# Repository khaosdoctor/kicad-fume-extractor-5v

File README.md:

# Fume Extractor 5V

KiCad project for a small, battery-powered fume extractor: a 9V battery feeds an
L7805 linear regulator to drive a 5V fan through a BC337 transistor, with a
potentiometer for speed control, a trimmer for calibration, a power switch and
an LED indicator.

This is my first electronics project, so it's a work in progress. Expect
multiple revisions as the design gets refined.

## PCB preview

| Top | Bottom |
|-----|--------|
|  |  |

## Hardware overview

Interactive BOM: [khaosdoctor.github.io/kicad-fume-extractor-5v/bom/ibom.html](https://khaosdoctor.github.io/kicad-fume-extractor-5v/bom/ibom.html)

| Ref  | Part                     | Function                        |
|------|--------------------------|----------------------------------|
| BT1  | 9V battery cell          | Power source                     |
| U1   | L7805ACV                 | 5V linear regulator               |
| Q1   | BC337                    | Fan drive transistor              |
| J1   | 2-pin connector          | Fan output                        |
| RV1  | 500R potentiometer       | Fan speed control                 |
| RV2  | 1K trimmer               | Calibration                       |
| R1   | 350R resistor            | Bias/current limiting             |
| C1/C2| Capacitors               | Regulator input/output filtering  |
| D1   | LED                      | Power indicator                   |
| SW1  | SPST switch              | Power on/off                      |

The board is a 2-layer PCB designed in KiCad 10.

## Generating manufacturing files with KiBot

This project uses [KiBot](https://github.com/INTI-CMNB/KiBot) to generate
gerbers, drill files, pick & place, BOM, documentation and 3D outputs
straight from the KiCad source files, via `kibot.yaml`.

### Outputs produced

| Group           | Outputs                                                        | Directory              |
|-----------------|------------------------------------------------------------------|-------------------------|
| `fabrication`   | Gerbers, Excellon drill files                                    | `Manufacturing/Gerbers` |
| `assembly`      | Pick & place position file, BOM (CSV)                            | `Manufacturing/Assembly`|
| `documentation` | Schematic PDF, PCB PDF, interactive HTML BOM                      | `Documentation`, `bom`  |
| `3d`            | STEP model, top/bottom 3D renders                                 | `3D`                    |

A zipped bundle of gerbers + drill files ready to send to a fab house is also
produced under `Manufacturing/manufacturing_zip.zip`. A JLCPCB-specific BOM
(`bom_jlcpcb`) filtered to parts with an LCSC part number is available but not
run by default.

### Running locally

Install KiCad (10.x) and KiBot, then from the repository root run:

```bash
pip install kibot
kibot -e "fume Extractor.kicad_sch" -b "fume Extractor.kicad_pcb"
```

To generate a single group or output, pass its name as a target, e.g.:

```bash
kibot -e "fume Extractor.kicad_sch" -b "fume Extractor.kicad_pcb" fabrication
```

### Running with Docker

No local KiCad/KiBot install is required if you have Docker:

```bash
docker run --rm -v "$(pwd)":/mnt ghcr.io/inti-cmnb/kicad10_auto_full:latest \
  kibot -e "fume Extractor.kicad_sch" -b "fume Extractor.kicad_pcb"
```

### Running in CI

The [`kibot.yml`](.github/workflows/kibot.yml) workflow runs KiBot on every
push and pull request and uploads the generated files as a build artifact.
On pushes to `main` it also commits the refreshed `bom/ibom.html`,
`3D/render_top.png` and `3D/render_bottom.png` back to the repo, which is
what keeps the PCB preview and interactive BOM link above up to date.

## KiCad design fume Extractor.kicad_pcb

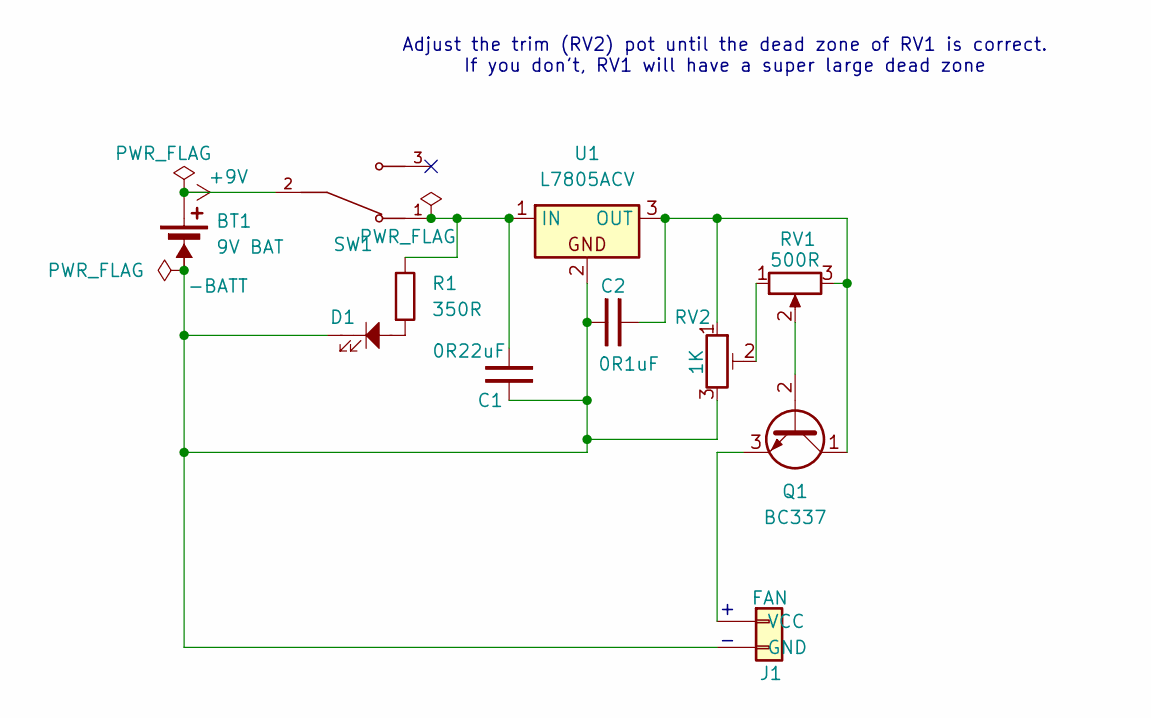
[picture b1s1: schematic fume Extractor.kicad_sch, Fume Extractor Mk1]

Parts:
BT1: 9V BAT; Molex_KK-254_AE-6410-02A_1x02_P2.54mm_Vertical
C1: 0R22uF; C_Rect_L10.0mm_W4.0mm_P7.50mm_MKS4
C2: 0R1uF; C_Disc_D3.0mm_W2.0mm_P2.50mm
D1: LED_3mm; LED_D3.0mm
J1: FAN; Molex_KK-254_AE-6410-02A_1x02_P2.54mm_Vertical
Q1: BC337; TO-92_Inline
R1: 350R; R_Axial_DIN0207_L6.3mm_D2.5mm_P10.16mm_Horizontal
RV1: 500R; SolderWire-0.5sqmm_1x03_P4.6mm_D0.9mm_OD2.1mm
RV2: 1K; Potentiometer_Bourns_3266W_Vertical
SW1: SW_SPST; Switch_Toggle_SPDT_SubMini; PARTREV E
U1: L7805ACV; TO-220-3_Vertical

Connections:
+9V: BT1.1 (+), SW1.2
-BATT: BT1.2 (-), C1.2, C2.1, D1.1, J1.2 (GND), RV2.3, U1.2
unnamed: D1.2, R1.1
unnamed: J1.1 (VCC), Q1.3 (E)
unnamed: Q1.2 (B), RV1.2
unnamed: C2.2, Q1.1 (C), RV1.3, RV2.1, U1.3 (OUT)
unnamed: RV1.1, RV2.2
unnamed: C1.1, R1.2, SW1.1, U1.1 (IN)

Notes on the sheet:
Adjust the trim (RV2) pot until the dead zone of RV1 is correct. If you don't, RV1 will have a super large dead zone

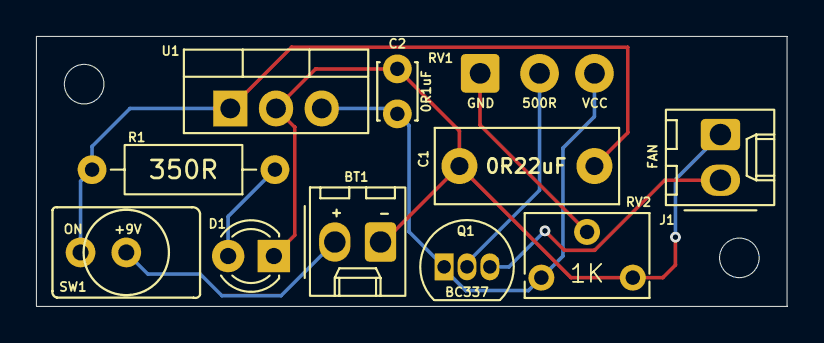
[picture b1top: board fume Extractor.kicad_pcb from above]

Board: 2 copper layers, 41.7 x 15.0 mm, 11 parts (0 on the bottom side), 8 nets.
